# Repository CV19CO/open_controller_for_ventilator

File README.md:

# Open source controller board for ventilators

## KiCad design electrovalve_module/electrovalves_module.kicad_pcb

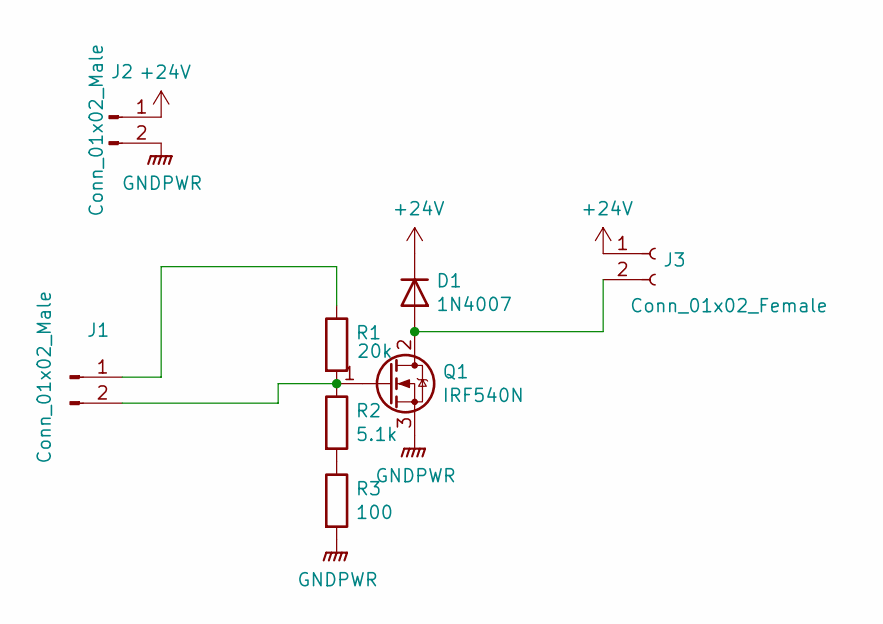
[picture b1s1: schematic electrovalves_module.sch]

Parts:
D1: 1N4007; D_DO-41_SOD81_P10.16mm_Horizontal
J1, J2: Conn_01x02_Male; TerminalBlock_bornier-2_P5.08mm
J3: Conn_01x02_Female; TerminalBlock_bornier-2_P5.08mm
Q1: IRF540N; TO-220-3_Vertical
R1: 20k; R_Axial_DIN0207_L6.3mm_D2.5mm_P7.62mm_Horizontal
R2: 5.1k; R_Axial_DIN0207_L6.3mm_D2.5mm_P7.62mm_Horizontal
R3: 100; R_Axial_DIN0207_L6.3mm_D2.5mm_P7.62mm_Horizontal

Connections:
+24V: D1.1 (K), J2.1, J3.1
GNDPWR: J2.2, Q1.3 (S), R3.2
unnamed: D1.2 (A), J3.2, Q1.2 (D)
unnamed: J1.1, R1.1
unnamed: J1.2, Q1.1 (G), R1.2, R2.1
unnamed: R2.2, R3.1

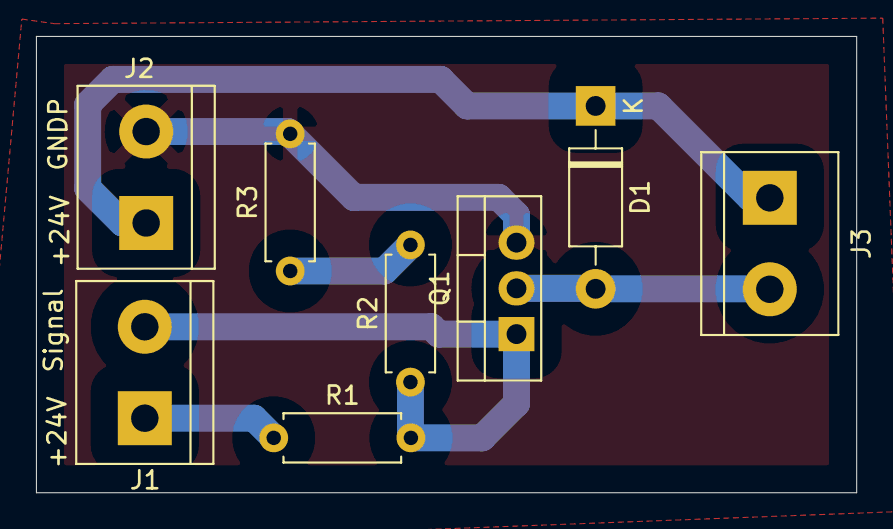
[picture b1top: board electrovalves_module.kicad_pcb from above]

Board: 2 copper layers, 45.6 x 25.3 mm, 8 parts (0 on the bottom side), 6 nets.

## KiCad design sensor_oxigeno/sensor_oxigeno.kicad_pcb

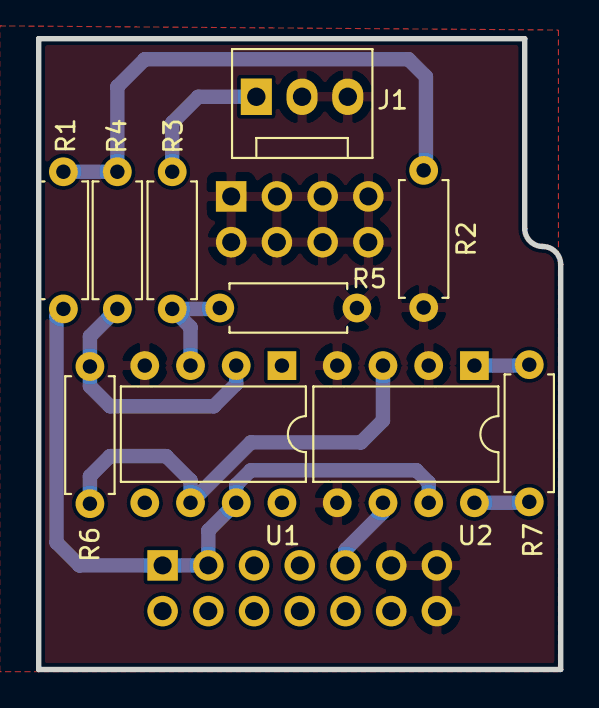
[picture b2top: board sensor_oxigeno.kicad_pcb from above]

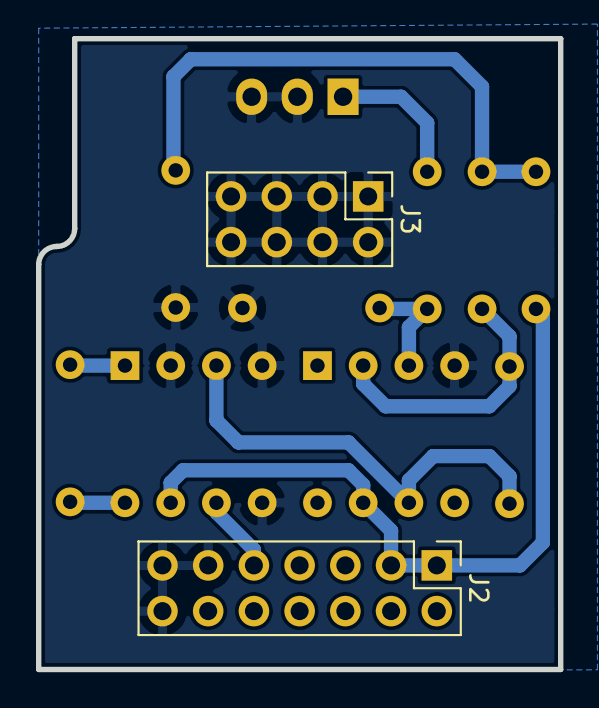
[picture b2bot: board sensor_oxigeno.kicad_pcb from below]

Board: 4 copper layers, 29.0 x 35.0 mm, 12 parts (2 on the bottom side), 10 nets.

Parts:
J1: Conn_01x02_Female; FanPinHeader_1x03_P2.54mm_Vertical
J2: Conn_02x07_Odd_Even; PinHeader_2x07_P2.54mm_Vertical
J3: Conn_02x04_Odd_Even; PinHeader_2x04_P2.54mm_Vertical
R1: 25.3 k; R_Axial_DIN0207_L6.3mm_D2.5mm_P7.62mm_Horizontal
R2: 100; R_Axial_DIN0207_L6.3mm_D2.5mm_P7.62mm_Horizontal
R3, R4, R5, R6: 10k; R_Axial_DIN0207_L6.3mm_D2.5mm_P7.62mm_Horizontal
R7: 50; R_Axial_DIN0207_L6.3mm_D2.5mm_P7.62mm_Horizontal
U1: LM318N; DIP-8_W7.62mm
U2: INA128; DIP-8_W7.62mm

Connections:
+3V3: J2.1, J2.3, R1.2, U1.7, U2.7
/Analog: J2.9, U2.6
GND: J1.2, J1.3, J2.11, J2.13, J2.14, J3.1, J3.2, J3.3, J3.4, J3.5, J3.6, J3.7, J3.8, R2.2, R5.1, U1.4, U2.2, U2.4, U2.5
unnamed: J1.1, R3.2
unnamed: R1.1, R2.1, R4.2
unnamed: R3.1, R5.2, U1.3
unnamed: R4.1, R6.2, U1.2
unnamed: R6.1, U1.6, U2.3
unnamed: R7.1, U2.1
unnamed: R7.2, U2.8

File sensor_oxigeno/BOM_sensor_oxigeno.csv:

"Source:","/home/jaiber/proyectos/respirador/repos/open_controller_for_ventilator/sensor_oxigeno/sensor_oxigeno.sch"
"Date:","jue 26 may 2022 21:42:56"
"Tool:","Eeschema 5.1.12-84ad8e8a86~92~ubuntu20.04.1"
"Generator:","/usr/share/kicad/plugins/bom_csv_grouped_by_value.py"
"Component Count:","12"

"Individual Components:"

"Item","Qty","Reference(s)","Value","LibPart","Footprint","Datasheet"
"","","J1","Conn_01x02_Female","Connector:Conn_01x03_Male","Connector:FanPinHeader_1x03_P2.54mm_Vertical","~"
"","","J2","Conn_02x07_Odd_Even","Connector_Generic:Conn_02x07_Odd_Even","Connector_PinHeader_2.54mm:PinHeader_2x07_P2.54mm_Vertical","~"
"","","J3","Conn_02x04_Odd_Even","Connector_Generic:Conn_02x04_Odd_Even","Connector_PinHeader_2.54mm:PinHeader_2x04_P2.54mm_Vertical","~"
"","","R1","25.3 k","Device:R","Resistor_THT:R_Axial_DIN0207_L6.3mm_D2.5mm_P7.62mm_Horizontal","~"
"","","R2","100","Device:R","Resistor_THT:R_Axial_DIN0207_L6.3mm_D2.5mm_P7.62mm_Horizontal","~"
"","","R3","10k","Device:R","Resistor_THT:R_Axial_DIN0207_L6.3mm_D2.5mm_P7.62mm_Horizontal","~"
"","","R4","10k","Device:R","Resistor_THT:R_Axial_DIN0207_L6.3mm_D2.5mm_P7.62mm_Horizontal","~"
"","","R5","10k","Device:R","Resistor_THT:R_Axial_DIN0207_L6.3mm_D2.5mm_P7.62mm_Horizontal","~"
"","","R6","10k","Device:R","Resistor_THT:R_Axial_DIN0207_L6.3mm_D2.5mm_P7.62mm_Horizontal","~"
"","","R7","50","Device:R","Resistor_THT:R_Axial_DIN0207_L6.3mm_D2.5mm_P7.62mm_Horizontal","~"
"","","U1","LM318N","Amplifier_Operational:LM318N","Package_DIP:DIP-8_W7.62mm","http://www.ti.com/lit/ds/symlink/lm318-n.pdf"
"","","U2","INA128","Amplifier_Instrumentation:INA128","Package_DIP:DIP-8_W7.62mm","http://www.ti.com/lit/ds/symlink/ina128.pdf"



"Collated Components:"

"Item","Qty","Reference(s)","Value","LibPart","Footprint","Datasheet"
"1","1","J1","Conn_01x02_Female","Connector:Conn_01x03_Male","Connector:FanPinHeader_1x03_P2.54mm_Vertical","~"
"2","1","J2","Conn_02x07_Odd_Even","Connector_Generic:Conn_02x07_Odd_Even","Connector_PinHeader_2.54mm:PinHeader_2x07_P2.54mm_Vertical","~"
"3","1","J3","Conn_02x04_Odd_Even","Connector_Generic:Conn_02x04_Odd_Even","Connector_PinHeader_2.54mm:PinHeader_2x04_P2.54mm_Vertical","~"
"4","1","R1","25.3 k","Device:R","Resistor_THT:R_Axial_DIN0207_L6.3mm_D2.5mm_P7.62mm_Horizontal","~"
"5","1","R2","100","Device:R","Resistor_THT:R_Axial_DIN0207_L6.3mm_D2.5mm_P7.62mm_Horizontal","~"
"6","4","R3, R4, R5, R6","10k","Device:R","Resistor_THT:R_Axial_DIN0207_L6.3mm_D2.5mm_P7.62mm_Horizontal","~"
"7","1","R7","50","Device:R","Resistor_THT:R_Axial_DIN0207_L6.3mm_D2.5mm_P7.62mm_Horizontal","~"
"8","1","U1","LM318N","Amplifier_Operational:LM318N","Package_DIP:DIP-8_W7.62mm","http://www.ti.com/lit/ds/symlink/lm318-n.pdf"
"9","1","U2","INA128","Amplifier_Instrumentation:INA128","Package_DIP:DIP-8_W7.62mm","http://www.ti.com/lit/ds/symlink/ina128.pdf"

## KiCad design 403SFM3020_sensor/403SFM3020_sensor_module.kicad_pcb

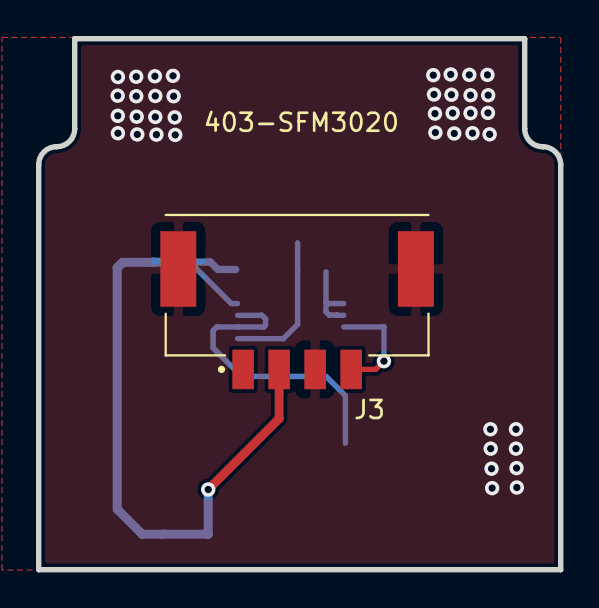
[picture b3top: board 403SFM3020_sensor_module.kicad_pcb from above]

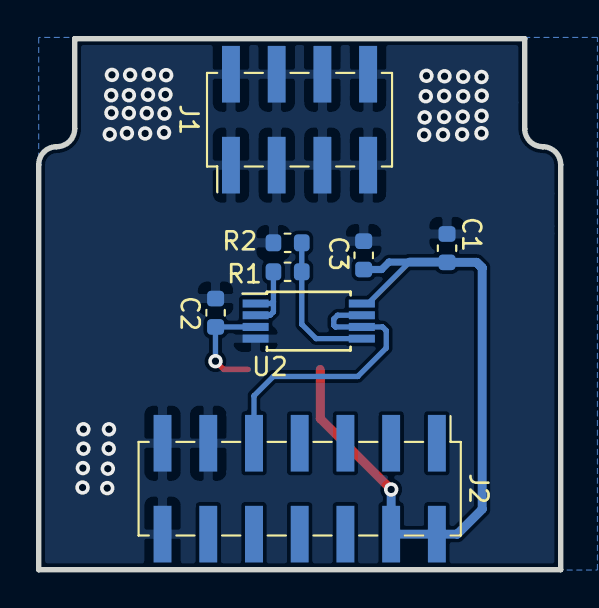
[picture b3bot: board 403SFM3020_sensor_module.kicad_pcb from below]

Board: 4 copper layers, 29.0 x 29.5 mm, 9 parts (8 on the bottom side), 7 nets.

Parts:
C1, C3: 0.1u; C_0603_1608Metric
C2: 1n; C_0603_1608Metric
J1: Conn_02x04_Odd_Even; PinHeader_2x04_P2.54mm_Vertical_SMD
J2: Conn_02x07_Odd_Even; PinHeader_2x07_P2.54mm_Vertical_SMD
J3: Conn_01x05_Female; MOLEX_5600200430
R1: 11k3; R_0603_1608Metric
R2: 22k; R_0603_1608Metric
U2: LM358; TSSOP-8_4.4x3mm_P0.65mm

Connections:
+3V3: J2.1, J2.3
+5V: C1.1, C3.1, J2.2, J2.4, J3.2, U2.8
/Analog: J2.9, U2.6, U2.7
GND: C1.2, C2.2, C3.2, J1.1, J1.2, J1.3, J1.4, J1.5, J1.6, J1.7, J1.8, J2.11, J2.13, J2.14, J3.3, J3.S1, J3.S2, R2.2, U2.4
unnamed: C2.1, J3.4, U2.3
unnamed: R1.1, R2.1, U2.5
unnamed: R1.2, U2.1, U2.2

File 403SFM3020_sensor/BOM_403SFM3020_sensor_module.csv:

Item,Qty,Reference(s),Value,Footprint,DigiKey
1,2,"C1, C3",0.1u,Capacitor_SMD:C_0603_1608Metric,732-7939-1-ND
2,1,C2,1n,Capacitor_SMD:C_0603_1608Metric,311-4053-1-ND
3,1,J1,Conn_02x04_Odd_Even,Connector_PinHeader_2.54mm:PinHeader_2x04_P2.54mm_Vertical_SMD,609-6367-ND
4,1,J2,Conn_02x07_Odd_Even,Connector_PinHeader_2.54mm:PinHeader_2x07_P2.54mm_Vertical_SMD,609-6365-ND
5,1,J3,Conn_01x05_Female,SMD_project:MOLEX_5600200430,WM17822CT-ND
6,1,J3,Conn_01x05_Female,SMD_project:MOLEX_5600200430,WM8688-ND
7,8,J3,Conn_01x05_Female,SMD_project:MOLEX_5600200430,WM4561CT-ND
8,1,R1,11k3,Resistor_SMD:R_0603_1608Metric,A102208CT-ND
9,1,R2,22k,Resistor_SMD:R_0603_1608Metric,A103066CT-ND
10,1,U2,LM358,Package_SO:TSSOP-8_4.4x3mm_P0.65mm,296-51268-1-ND

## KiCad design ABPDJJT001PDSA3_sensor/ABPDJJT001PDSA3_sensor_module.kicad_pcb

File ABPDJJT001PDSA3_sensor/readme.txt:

Sensor: ABPDJJT001PDSA3 
Mouser: https://co.mouser.com/ProductDetail/785-ABPDJJT001PDSA3
Datasheet: https://co.mouser.com/datasheet/2/187/honeywell-sensing-basic-board-mount-pressure-abp-s-1662208.pdf

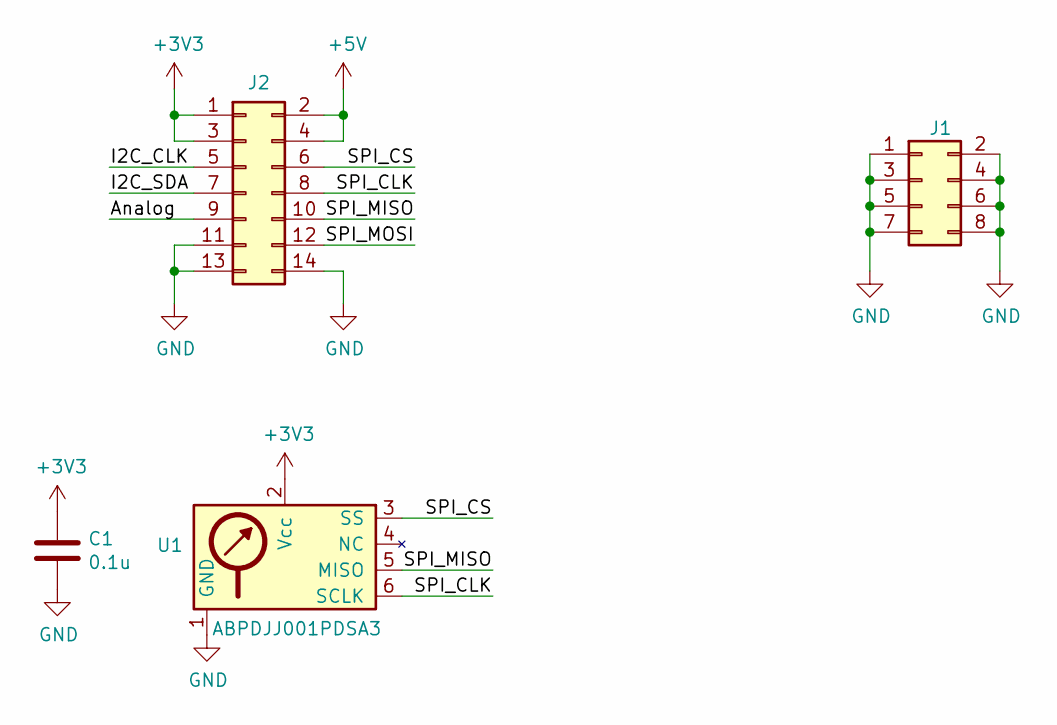
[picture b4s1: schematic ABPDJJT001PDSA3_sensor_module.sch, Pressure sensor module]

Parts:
C1: 0.1u; C_0603_1608Metric; DigiKey 1276-1258-1-ND
J1: Conn_02x04_Odd_Even; PinHeader_2x04_P2.54mm_Vertical_SMD; DigiKey 609-6367-ND
J2: Conn_02x07_Odd_Even; PinHeader_2x07_P2.54mm_Vertical_SMD; DigiKey 609-6365-ND
U1: ABPDJJ001PDSA3; DIP_JJ

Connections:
+3V3: C1.1, J2.1, J2.3, U1.2 (Vcc)
+5V: J2.2, J2.4
/Analog: J2.9
/I2C_CLK: J2.5
/I2C_SDA: J2.7
/SPI_CLK: J2.8, U1.6 (SCLK)
/SPI_CS: J2.6, U1.3 (SS)
/SPI_MISO: J2.10, U1.5 (MISO)
/SPI_MOSI: J2.12
GND: C1.2, J1.1, J1.2, J1.3, J1.4, J1.5, J1.6, J1.7, J1.8, J2.11, J2.13, J2.14, U1.1 (GND)

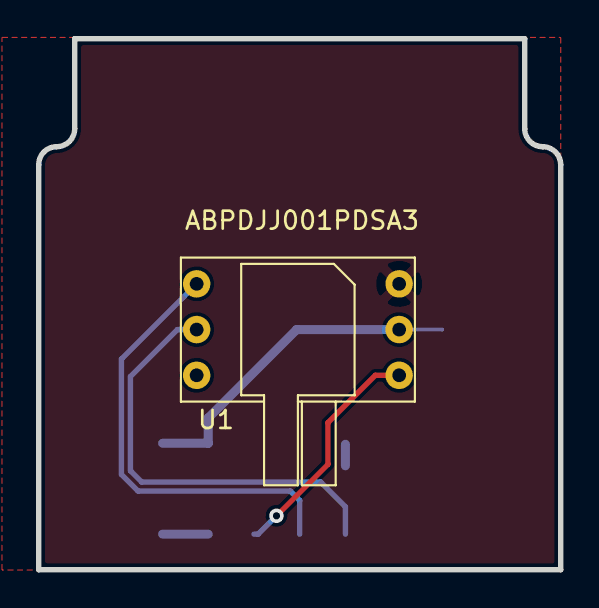
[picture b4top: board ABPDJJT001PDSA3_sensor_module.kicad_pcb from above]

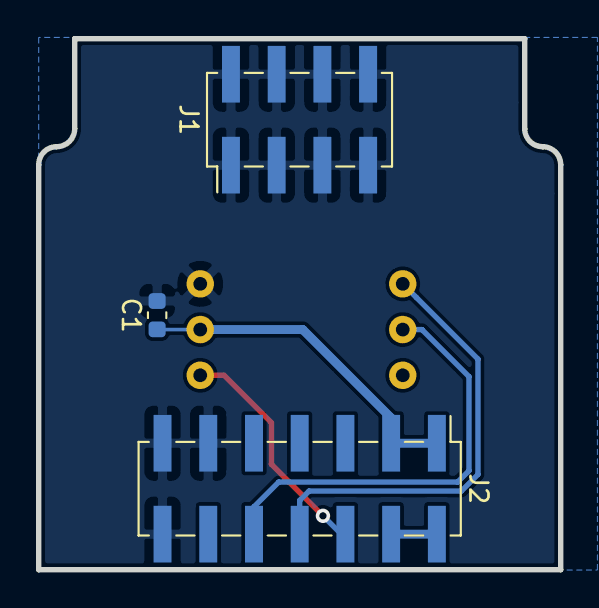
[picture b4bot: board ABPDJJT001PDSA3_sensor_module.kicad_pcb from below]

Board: 4 copper layers, 29.0 x 29.5 mm, 4 parts (3 on the bottom side), 6 nets.

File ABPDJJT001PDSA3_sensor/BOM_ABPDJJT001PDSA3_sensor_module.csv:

Reference, Quantity, Value, Footprint, Datasheet, DigiKey
C1 ,1,"0.1u","Capacitor_SMD:C_0603_1608Metric","~","1276-1258-1-ND"
J1 ,1,"Conn_02x04_Odd_Even","Connector_PinHeader_2.54mm:PinHeader_2x04_P2.54mm_Vertical_SMD","~","609-6367-ND"
J2 ,1,"Conn_02x07_Odd_Even","Connector_PinHeader_2.54mm:PinHeader_2x07_P2.54mm_Vertical_SMD","~","609-6365-ND"
U1 ,1,"ABPDJJ001PDSA3","TH_project:DIP_JJ",""

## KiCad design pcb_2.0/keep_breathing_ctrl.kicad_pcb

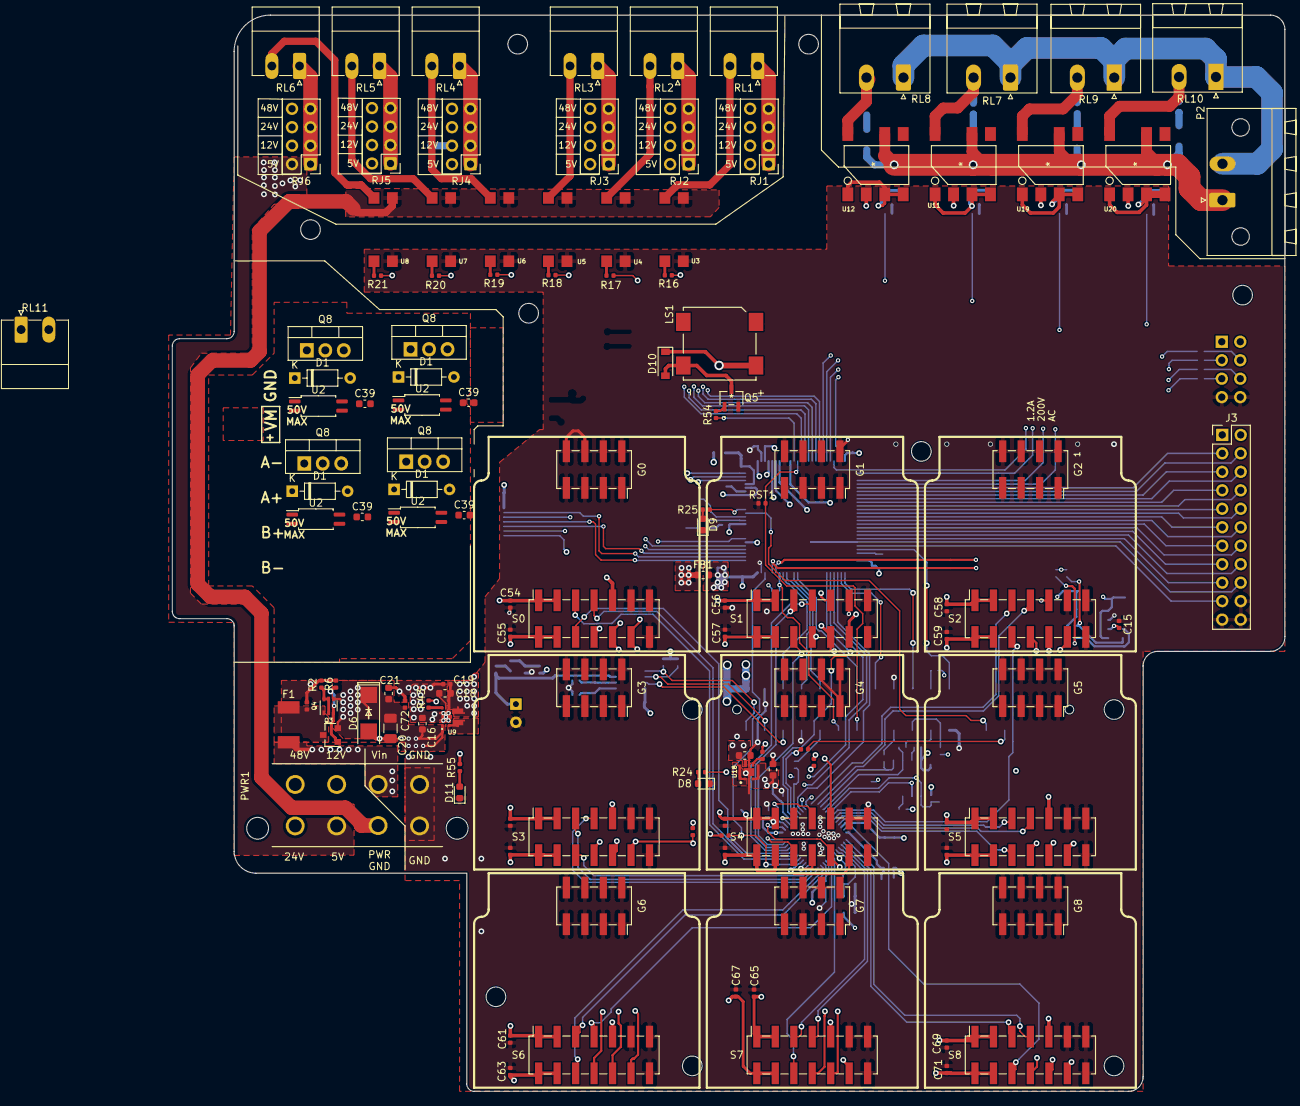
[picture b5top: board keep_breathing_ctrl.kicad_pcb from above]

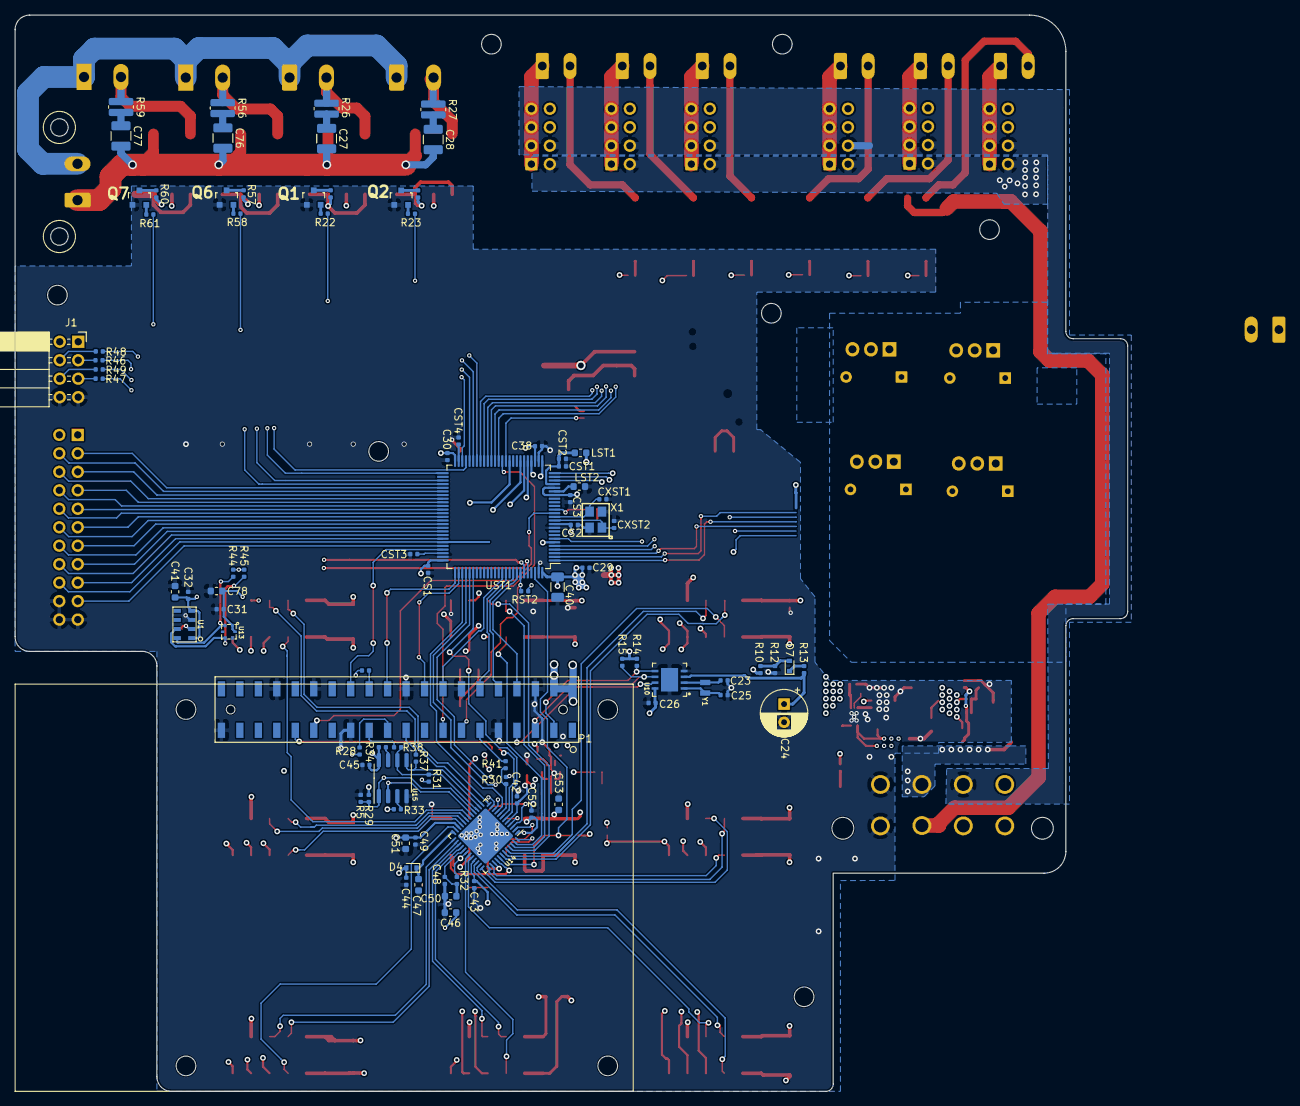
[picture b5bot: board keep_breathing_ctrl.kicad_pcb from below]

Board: 4 copper layers, 153.0 x 148.0 mm, 226 parts (91 on the bottom side), 190 nets.

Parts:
C15, C31, C32: 100nF; C_0402_1005Metric
C16, C18: 10u; C_0603_1608Metric
C17: 1uF; C_0402_1005Metric
C19, C42, C44: 0.1u; C_0402_1005Metric
C20: 100uF; R_1206_3216Metric
C21: 47uF; R_0603_1608Metric
C23, C25: 4pF; C_0402_1005Metric
C24: JUWT1105MCD; CP_Radial_D6.3mm_P2.50mm
C26, C29, C30, C38, C54, C55, C56, C57, C58, C59, C60, C61, C62, C63, C64, C65, C66, C67, C68, C69, C70, C71: 0.1uF; C_0402_1005Metric
C27, C28, C76, C77: 0.1u 250V; C_1210_3225Metric
C39, C39#2, C39#3, C39#4: 1uF; C_0603_1608Metric
C40: 4.7uF; C_1206_3216Metric
C41, C75, C78: 10uF; C_0603_1608Metric
C43, C45, C48, C49, C52: 0.1u; R_0402_1005Metric
C46, C50, C51, C53: 4.7u; R_0603_1608Metric
C47, C73: 4.7u; C_0603_1608Metric
C72: 100nF; R_0402_1005Metric
CS1, CS2, CS3: 0.1uF; C_0402_1005Metric
CST1: 0.1uF; C_0402_1005Metric
CST2: 1uF; C_0402_1005Metric
CST3, CST4: 2.2uF; C_0402_1005Metric
CXST1, CXST2: 22pF; C_0402_1005Metric
D1, D1#2, D1#3, D1#4: 1N4148; D_DO-35_SOD27_P7.62mm_Horizontal
D4: CDBU0520; D_SOD-523
D6: SMBJ5.0A-TR; DO-214AA
D7: 1SS389,L3F; D_SOD-523
D8, D9, D11: LED; LED_0603_1608Metric
D10: 1N4148; D_SOD-123
F1: MF-MSMF250/X; PTC
FB1: Ferrite_Bead_Small; R_0603_1608Metric
G0, G1, G2, G3, G4, G5, G6, G7, G8: Conn_01x03; PinSocket_2x04_P2.54mm_Vertical_SMD
H1, H2, H3, H4, H5, H6, H7, H8, H9, H10, H11: MountingHole; MountingHole_2.7mm_M2.5
J1: Conn_02x04_Odd_Even; PinSocket_2x04_P2.54mm_Horizontal
J3: Conn_02x11_Odd_Even; PinHeader_2x11_P2.54mm_Vertical
LS1: CSS-95B30-SMT; CUI_CSS-95B30-SMT
LST1, LST2: 2A 120 ohm; R_0603_1608Metric
P1: CONN_RASPBERRY; SMD_CONN_2x20
P2: Conn_01x04_Female; PhoenixContact_MSTB_2,5_2-GF_1x02_P5.00mm_Horizontal_Thread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
PWR1: Conn_01x03; 10142708-08200LF
Q1, Q2, Q6, Q7: PN2222; SOT23_Transistor
Q3: DMG2305UX; SOT-23
Q4: BCM857BS; SOT-363_SC-70-6
Q5: 2SC3325-Y
Q8, Q8#2, Q8#3, Q8#4: IRF540N; TO-220-3_Vertical
R2, R42, R43, R44, R45: 10k; R_0402_1005Metric
R5, R29, R30, R31, R33, R34, R50, R51, R53: 10K; R_0402_1005Metric
R6: 47k; R_0402_1005Metric
R10: 450; R_0402_1005Metric
R12: 500; R_0402_1005Metric
R13, R28, R32, R37, R38, R40, R41, R46, R47, R48, R49, R52: 100; R_0402_1005Metric
R14, R15: 2.2k; R_0402_1005Metric
R16, R17, R18, R19, R20, R21, R23, R61: 200; R_0402_1005Metric
R22, R58: 330; R_0402_1005Metric
R24, R25, R55: 1k; R_0402_1005Metric
R26, R27, R56, R59: 100 1/2W; R_0612_1632Metric
R35, R36, R57, R60: 22; R_0402_1005Metric
R54: 180; R_0402_1005Metric
RJ1, RJ2, RJ3, RJ4, RJ5, RJ6: Conn_02x04_Odd_Even; PinHeader_2x04_P2.54mm_Vertical
RL1, RL2, RL3, RL4, RL5, RL6, RL11: Conn_01x04_Female; PhoenixContact_MC_1,5_2-G-3.81_1x02_P3.81mm_Horizontal
RL7, RL8, RL9, RL10: Conn_01x04_Female; PhoenixContact_MSTBA_2,5_2-G-5,08_1x02_P5.08mm_Horizontal
RST1, RST2: 10k; R_0402_1005Metric
S0, S1, S2, S3, S4, S5, S6, S7, S8: Conn_02x07_Counter_Clockwise; PinSocket_2x07_P2.54mm_Vertical_SMD
U1: MPL3115A2; 8LGA
U2, U2#2, U2#3, U2#4: TLP291; SOIC-4_4.55x2.6mm_P1.27mm
U3, U4, U5, U6, U7, U8: TLP240D; TLP240D_TP1
U9: XCL214B333; TOREX_XCL214B123DR
U10: PCF8523TK; HVSON8
U11, U12, U19, U20: AQH3223AX; AQH3223A
U13: HTS221; HLGA-6L
U14: ICE40UP5K-SG48ITR; QFN-48-1EP_7x7mm_P0.5mm_EP5.6x5.6mm
U15: GD25Q32CTIGR-Memory_Flash; SOIC-8_3.9x4.9mm_P1.27mm
U18: XCL206B123; CL-2025-02
UST1: STM32F427VIT6; LQFP-100_14x14mm_P0.5mm
X1: ABM8G
Y1: ABS06-107-32.768KHZ-T; ABS06-107

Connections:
1V2_ICE: C42.1, C75.1, R32.2, U14.5, U14.30, U18.3, U18.8
3V3_STM: C29.1, C30.1, C38.1, C39#4.1, C40.1, CS1.1, CS2.1, CS3.1, FB1.2, LST1.1, RST2.1, UST1.6, UST1.11, UST1.19, UST1.21, UST1.28, UST1.50, UST1.75, UST1.100
5V_R: PWR1.5, RJ1.2, RJ2.2, RJ3.2, RJ4.2, RJ5.2, RJ6.2
12V_R: PWR1.6, RJ1.4, RJ2.4, RJ3.4, RJ4.4, RJ5.4, RJ6.4
24V_R: PWR1.7, RJ1.6, RJ2.6, RJ3.6, RJ4.6, RJ5.6, RJ6.6
48V_R: PWR1.8, RJ1.8, RJ2.8, RJ3.8, RJ4.8, RJ5.8, RJ6.8
+2V5: C47.1, D4.1, U14.24
+3V3: C18.1, C19.1, C26.2, C31.1, C32.1, C41.1, C43.1, C44.1, C45.1, C46.1, C49.1, C51.1, C52.1, C53.1, C54.1, C56.1, C58.1, C60.1, C61.1, C64.1, C65.1, C68.1, C69.1, C78.1, D4.2, FB1.1, J1.1, J3.1, R14.2, R15.2, R29.2, R30.2, R31.2, R33.2, R34.2, R44.1, R45.1, R50.2, R51.2, R53.2, S0.1, S0.3, S1.1, S1.3, S2.1, S2.3, S3.1, S3.3, S4.1, S4.3, S5.1, S5.3, S6.1, S6.3, S7.1, S7.3, S8.1, S8.3, U1.1, U1.4, U9.4, U9.9, U10.8, U11.2, U12.2, U13.1, U13.6, U14.1, U14.22, U14.33, U15.8, U19.2, U20.2
+5V: C16.1, C20.1, C21.1, C55.1, C57.1, C59.1, C62.1, C63.1, C66.1, C67.1, C70.1, C71.1, C72.1, C73.1, D6.1, D10.1, J1.2, J3.2, LS1.P, P1.2, P1.4, Q3.2, Q4.4, R10.2, R42.2, R43.2, R55.2, S0.2, S0.4, S1.2, S1.4, S2.2, S2.4, S3.2, S3.4, S4.2, S4.4, S5.2, S5.4, S6.2, S6.4, S7.2, S7.4, S8.2, S8.4, U9.1, U18.6
/I2C/I2C_SCL: P1.5, R15.1, U10.6
/I2C/I2C_SDA: P1.3, R14.1, U10.5
/PSU/L1_Lx_1V2: U18.1, U18.7
/PSU/L1_Lx_3V3: U9.3, U9.8
/PSU/Q3S: C17.1, F1.2, Q3.3, Q4.1
/PSU/Vin: F1.1, PWR1.4
/Rapsberry/BOOT0: P1.13, RST2.2, UST1.94
/Rapsberry/BOOT1: P1.15, RST1.2, UST1.37
/Rapsberry/ICE_DONE: P1.31, R52.1
/Rapsberry/INT_RTC: P1.7, U10.7
/Rapsberry/JNRST: P1.12, UST1.90
/Rapsberry/JTCK: P1.22, UST1.76
/Rapsberry/JTDI: P1.18, UST1.77
/Rapsberry/JTDO: P1.16, UST1.89
/Rapsberry/JTMS: P1.26, UST1.72
/Rapsberry/MCU_NRST: P1.29, UST1.14
/Rapsberry/RST_ICE: P1.11, R41.1
/Rapsberry/RX_PI: P1.10, UST1.92
/Rapsberry/SPI_CLK: P1.23, R38.1
/Rapsberry/SPI_CS: P1.24, R40.1
/Rapsberry/SPI_MISO: P1.21, R28.1
/Rapsberry/SPI_MOSI: P1.19, R37.1
/STM32F4/Buzzer: R54.2, UST1.36
/STM32F4/LED: R25.2, UST1.15
/STM32F4/PA8: J3.15, UST1.67
/STM32F4/PA9: J3.16, UST1.68
/STM32F4/PA10: J3.17, UST1.69
/STM32F4/PA11: J3.18, UST1.70
/STM32F4/PA12: J3.19, UST1.71
/STM32F4/PC6: J3.11, UST1.63
/STM32F4/PC7: J3.12, UST1.64
/STM32F4/PC8: J3.13, UST1.65
/STM32F4/PC9: J3.14, UST1.66
/STM32F4/PD8: J3.3, UST1.55
/STM32F4/PD9: J3.4, UST1.56
/STM32F4/PD10: J3.5, UST1.57
/STM32F4/PD11: J3.6, UST1.58
/STM32F4/PD12: J3.7, UST1.59
/STM32F4/PD13: J3.8, UST1.60
/STM32F4/PD14: J3.9, UST1.61
/STM32F4/PD15: J3.10, UST1.62
/STM32F4/P_EV7: R21.2, UST1.38
/STM32F4/P_EV8: R20.2, UST1.39
/STM32F4/P_EV9: R19.2, UST1.40
/STM32F4/P_EV10: R18.2, UST1.41
/STM32F4/P_EV11: R17.2, UST1.42
/STM32F4/P_EV12: R16.2, UST1.43
/STM32F4/P_EV13: R23.2, UST1.44
/STM32F4/P_EV14: R22.2, UST1.45
/STM32F4/P_EV15: R58.2, UST1.46
/STM32F4/P_EV16: R61.2, UST1.48
/STM32F4/SPI2_MISO: R49.1, UST1.53
/STM32F4/SPI2_MOSI: R47.2, UST1.54
/STM32F4/SPI2_NSS_0: R46.2, UST1.51
/STM32F4/SPI2_SCK: R48.1, UST1.47
/STM32F4/SPI3_MISO: U14.10, UST1.79
/STM32F4/SPI3_MOSI: U14.11, UST1.80
/STM32F4/SPI3_NSS: U14.6, UST1.81
/STM32F4/SPI3_SCK: U14.9, UST1.78
/STM32F4/SPI4_NSS_1: R53.1, U14.41, UST1.98
/STM32F4/STM_UART_RX: P1.8, UST1.93
/STM32F4/VDDAST: CST1.1, CST2.1, LST1.2, UST1.22
/SensorShields/ANALOG_0: S0.9, UST1.25
/SensorShields/ANALOG_1: S1.9, UST1.26
/SensorShields/ANALOG_2: S2.9, UST1.35
/SensorShields/ANALOG_3: S3.9, UST1.24
/SensorShields/ANALOG_4: S4.9, UST1.29
/SensorShields/ANALOG_5: S5.9, UST1.32
/SensorShields/ANALOG_6: S6.9, UST1.23
/SensorShields/ANALOG_7: S7.9, UST1.30
/SensorShields/ANALOG_8: S8.9, UST1.31
/SensorShields/CDONE: R24.2, R52.2, U14.7
/SensorShields/CRESET_N: R30.1, R41.2, U14.8
/SensorShields/FPGA_SI: R28.2, U14.17, U15.2
/SensorShields/FPGA_SO: R37.2, U14.14, U15.5
/SensorShields/FT_SCK: R31.1, R38.2, U14.15, U15.6
/SensorShields/FT_SSn: R5.2, R29.1, R40.2, U14.16, U15.1
/SensorShields/I2C_CLK_0: S0.5, U14.42
/SensorShields/I2C_CLK_1: S1.5, U14.46
/SensorShields/I2C_CLK_2: S2.5, U14.12
/SensorShields/I2C_CLK_3: S3.5, U14.37
/SensorShields/I2C_CLK_4: S4.5, U14.4
/SensorShields/I2C_CLK_5: S5.5, U14.19
/SensorShields/I2C_CLK_6: S6.5, U14.34
/SensorShields/I2C_CLK_7: S7.5, U14.28
/SensorShields/I2C_CLK_8: S8.5, U14.26
/SensorShields/I2C_SDA_0: S0.7, U14.43
/SensorShields/I2C_SDA_1: S1.7, U14.45
/SensorShields/I2C_SDA_2: S2.7, U14.13
/SensorShields/I2C_SDA_3: S3.7, U14.36
/SensorShields/I2C_SDA_4: S4.7, U14.3
/SensorShields/I2C_SDA_5: S5.7, U14.20
/SensorShields/I2C_SDA_6: S6.7, U14.32
/SensorShields/I2C_SDA_7: S7.7, U14.27
/SensorShields/I2C_SDA_8: S8.7, U14.25
/SensorShields/SPI_CLK: R50.1, S0.8, S1.8, S2.8, S3.8, S4.8, S5.8, S6.8, S7.8, S8.8, U14.39
/SensorShields/SPI_CS_0: S0.6, U14.44
/SensorShields/SPI_CS_1: S1.6, U14.47
/SensorShields/SPI_CS_2: S2.6, U14.18
/SensorShields/SPI_CS_3: S3.6, U14.38
/SensorShields/SPI_CS_4: S4.6, U14.48
/SensorShields/SPI_CS_5: S5.6, U14.21
/SensorShields/SPI_CS_6: S6.6, U14.35
/SensorShields/SPI_CS_7: S7.6, U14.31
/SensorShields/SPI_CS_8: S8.6, U14.23
/SensorShields/SPI_MISO: S0.10, S1.10, S2.10, S3.10, S4.10, S5.10, S6.10, S7.10, S8.10, U14.2
/SensorShields/SPI_MOSI: R51.1, S0.12, S1.12, S2.12, S3.12, S4.12, S5.12, S6.12, S7.12, S8.12, U14.40
/SensorShields/VCC_PLL: C48.1, C50.1, R32.1, U14.29
/Sensors/SCL: R44.2, U1.8, U13.2, UST1.95
/Sensors/SDA: R45.2, U1.7, U13.4, UST1.96
GND: C15.2, C16.2, C17.2, C18.2, C19.2, C20.2, C21.2, C23.1, C24.2, C25.2, C26.1, C29.2, C30.2, C31.2, C32.2, C38.2, C39#4.2, C40.2, C41.2, C42.2, C43.2, C44.2, C45.2, C46.2, C47.2, C48.2, C49.2, C50.2, C51.2, C52.2, C53.2, C54.2, C55.2, C56.2, C57.2, C58.2, C59.2, C60.2, C61.2, C62.2, C63.2, C64.2, C65.2, C66.2, C67.2, C68.2, C69.2, C70.2, C71.2, C72.2, C73.2, C75.2, C78.2, CS1.2, CS2.2, CS3.2, CST1.2, CST2.2, CST3.1, CST4.1, CXST1.2, CXST2.2, D6.2, D8.1, D9.1, D11.1, G0.1, G0.2, G0.3, G0.4, G0.5, G0.6, G0.7, G0.8, G1.1, G1.2, G1.3, G1.4, G1.5, G1.6, G1.7, G1.8, G2.1, G2.2, G2.3, G2.4, G2.5, G2.6, G2.7, G2.8, G3.1, G3.2, G3.3, G3.4, G3.5, G3.6, G3.7, G3.8, G4.1, G4.2, G4.3, G4.4, G4.5, G4.6, G4.7, G4.8, G5.1, G5.2, G5.3, G5.4, G5.5, G5.6, G5.7, G5.8, G6.1, G6.2, G6.3, G6.4, G6.5, G6.6, G6.7, G6.8, G7.1, G7.2, G7.3, G7.4, G7.5, G7.6, G7.7, G7.8, G8.1, G8.2, G8.3, G8.4, G8.5, G8.6, G8.7, G8.8, J1.7, J1.8, J3.20, J3.21, J3.22, LST2.2, P1.6, P1.9, P1.14, P1.20, P1.25, P1.30, P1.34, P1.39, PWR1.1, PWR1.2, Q1.1, Q2.1, Q5.2, Q6.1, Q7.1, R2.2, R5.1, R6.2, R12.1, RST1.1, S0.11, S0.13, S0.14, S1.11, S1.13, S1.14, S2.11, S2.13, S2.14, S3.11, S3.13, S3.14, S4.11, S4.13, S4.14, S5.11, S5.13, S5.14, S6.11, S6.13, S6.14, S7.11, S7.13, S7.14, S8.11, S8.13, S8.14, U1.3, U2#4.2, U3.2, U4.2, U5.2, U6.2, U7.2, U8.2, U9.5, U9.7, U10.4, U10.PAD, U13.5, U14.49, U15.4, U18.2, U18.5, U18.PAD, UST1.10, UST1.27, UST1.74, UST1.99, X1.2, X1.4
GNDPWR: PWR1.3, Q8#4.3, U3.3, U4.3, U5.3, U6.3, U7.3, U8.3
LINE: P2.2, RL7.1, RL8.1, RL9.1, RL10.1
NEUT: C27.2, C28.2, C76.2, C77.2, P2.1, U11.6, U12.6, U19.6, U20.6
unnamed: C15.1, U1.2
unnamed: C23.2, U10.2, Y1.1
unnamed: C24.1, R13.1, U10.3
unnamed: C25.1, U10.1, Y1.2
unnamed: C27.1, R26.2
unnamed: C28.1, R27.2
unnamed: C76.1, R56.2
unnamed: C77.1, R59.2
unnamed: CST3.2, UST1.73
unnamed: CST4.2, UST1.49
unnamed: CXST1.1, UST1.13, X1.3
unnamed: CXST2.1, UST1.12, X1.1
unnamed: D1#4.1, RL11.1
unnamed: D1#4.2, Q8#4.2, RL11.2
unnamed: D7.1, R13.2
unnamed: D7.2, R10.1, R12.2
unnamed: D8.2, R24.1
unnamed: D9.2, R25.1
unnamed: D10.2, LS1.N, Q5.3
unnamed: D11.2, R55.1
unnamed: J1.3, R46.1
unnamed: J1.4, R48.2
unnamed: J1.5, R47.1
unnamed: J1.6, R49.2
unnamed: LST2.1, UST1.20
unnamed: Q1.2, R22.1
unnamed: Q1.3, R35.2
unnamed: Q2.2, R23.1
unnamed: Q2.3, R36.2
unnamed: Q3.1, Q4.3, R6.1
unnamed: Q4.2, Q4.5, Q4.6, R2.1
unnamed: Q5.1, R54.1
unnamed: Q6.2, R58.1
unnamed: Q6.3, R57.2
unnamed: Q7.2, R61.1
unnamed: Q7.3, R60.2
unnamed: Q8#4.1, U2#4.3
unnamed: R16.1, U3.1
unnamed: R17.1, U4.1
unnamed: R18.1, U5.1
unnamed: R19.1, U6.1
unnamed: R20.1, U7.1
unnamed: R21.1, U8.1
unnamed: R26.1, RL7.2, U11.8
unnamed: R27.1, RL8.2, U12.8
unnamed: R33.1, U15.3
unnamed: R34.1, U15.7
unnamed: R35.1, U11.1, U11.3, U11.4
unnamed: R36.1, U12.1, U12.3, U12.4
unnamed: R42.1, U18.4
unnamed: R43.1, U9.6
unnamed: R56.1, RL9.2, U19.8
unnamed: R57.1, U19.1, U19.3, U19.4
unnamed: R59.1, RL10.2, U20.8
unnamed: R60.1, U20.1, U20.3, U20.4
unnamed: RJ1.1, RJ1.3, RJ1.5, RJ1.7, RL1.1
unnamed: RJ2.1, RJ2.3, RJ2.5, RJ2.7, RL2.1
unnamed: RJ3.1, RJ3.3, RJ3.5, RJ3.7, RL3.1
unnamed: RJ4.1, RJ4.3, RJ4.5, RJ4.7, RL4.1
unnamed: RJ5.1, RJ5.3, RJ5.5, RJ5.7, RL5.1
unnamed: RJ6.1, RJ6.3, RJ6.5, RJ6.7, RL6.1
unnamed: RL1.2, U3.4
unnamed: RL2.2, U4.4
unnamed: RL3.2, U5.4
unnamed: RL4.2, U6.4
unnamed: RL5.2, U7.4
unnamed: RL6.2, U8.4

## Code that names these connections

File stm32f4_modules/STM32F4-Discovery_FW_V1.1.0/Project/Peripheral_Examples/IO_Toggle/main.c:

/**
  ******************************************************************************
  * @file    IO_Toggle/main.c 
  * @author  MCD Application Team
  * @version V1.0.0
  * @date    19-September-2011
  * @brief   Main program body
  ******************************************************************************
  * @attention
  *
  * THE PRESENT FIRMWARE WHICH IS FOR GUIDANCE ONLY AIMS AT PROVIDING CUSTOMERS
  * WITH CODING INFORMATION REGARDING THEIR PRODUCTS IN ORDER FOR THEM TO SAVE
  * TIME. AS A RESULT, STMICROELECTRONICS SHALL NOT BE HELD LIABLE FOR ANY
  * DIRECT, INDIRECT OR CONSEQUENTIAL DAMAGES WITH RESPECT TO ANY CLAIMS ARISING
  * FROM THE CONTENT OF SUCH FIRMWARE AND/OR THE USE MADE BY CUSTOMERS OF THE
  * CODING INFORMATION CONTAINED HEREIN IN CONNECTION WITH THEIR PRODUCTS.
  *
  * <h2><center>&copy; COPYRIGHT 2011 STMicroelectronics</center></h2>
  ******************************************************************************  
  */ 

/* Includes ------------------------------------------------------------------*/
#include "stm32f4_discovery.h"
#include "stm32f4xx_gpio.h"
#include "stm32f4xx_rcc.h"
#include "stm32f4xx.h"

/** @addtogroup STM32F4_Discovery_Peripheral_Examples
  * @{
  */

/** @addtogroup IO_Toggle
  * @{
  */ 

/* Private typedef -----------------------------------------------------------*/
GPIO_InitTypeDef  GPIO_InitStructure;

/* Private define ------------------------------------------------------------*/
/* Private macro -------------------------------------------------------------*/
/* Private variables ---------------------------------------------------------*/
/* Private function prototypes -----------------------------------------------*/
void Delay(__IO uint32_t nCount);
/* Private functions ---------------------------------------------------------*/

/**
  * @brief  Main program
  * @param  None
  * @retval None
  */
int main(void)
{
  /*!< At this stage the microcontroller clock setting is already configured, 
       this is done through SystemInit() function which is called from startup
       file (startup_stm32f4xx.s) before to branch to application main.
       To reconfigure the default setting of SystemInit() function, refer to
        system_stm32f4xx.c file
     */

  /* GPIOD Periph clock enable */
  RCC_AHB1PeriphClockCmd(RCC_AHB1Periph_GPIOD, ENABLE);

  /* Configure PD12, PD13, PD14 and PD15 in output pushpull mode */
  GPIO_InitStructure.GPIO_Pin = GPIO_Pin_12 | GPIO_Pin_13| GPIO_Pin_14| GPIO_Pin_15;
  GPIO_InitStructure.GPIO_Mode = GPIO_Mode_OUT;
  GPIO_InitStructure.GPIO_OType = GPIO_OType_PP;
  GPIO_InitStructure.GPIO_Speed = GPIO_Speed_100MHz;
  GPIO_InitStructure.GPIO_PuPd = GPIO_PuPd_NOPULL;
  GPIO_Init(GPIOD, &GPIO_InitStructure);

  // Enable clock for GPIOA
    RCC_AHB1PeriphClockCmd(RCC_AHB1Periph_GPIOA, ENABLE);
  // Configure PA0 as push-pull output
    GPIO_InitStructure.GPIO_Pin = GPIO_Pin_0 | GPIO_Pin_1;
    GPIO_InitStructure.GPIO_Speed = GPIO_Speed_100MHz;
    GPIO_InitStructure.GPIO_Mode = GPIO_Mode_OUT;
    GPIO_InitStructure.GPIO_OType = GPIO_OType_PP;
    GPIO_Init(GPIOA, &GPIO_InitStructure);

  while (1)
  {

        /* Toggle LED on PA0 */
        // Reset bit will turn on LED (because the logic is interved)
        GPIO_ResetBits(GPIOA, GPIO_Pin_0);
        Delay(0x2FFFFF);
        GPIO_ResetBits(GPIOA, GPIO_Pin_1);
        Delay(0x2FFFFF);
        // Set bit will turn off LED (because the logic is interved)
        GPIO_SetBits(GPIOA, GPIO_Pin_0);
        Delay(0x2FFFFF);
        GPIO_SetBits(GPIOA, GPIO_Pin_1);
        Delay(0x2FFFFF);



    /* PD12 to be toggled */
//    GPIO_SetBits(GPIOD, GPIO_Pin_12);
    
    /* Insert delay */
//    Delay(0x3FFFFF);
    
    /* PD13 to be toggled */
//    GPIO_SetBits(GPIOD, GPIO_Pin_13);
    
    /* Insert delay */
//    Delay(0x3FFFFF);
  
    /* PD14 to be toggled */
//    GPIO_SetBits(GPIOD, GPIO_Pin_14);
    
    /* Insert delay */
//    Delay(0x3FFFFF);
    
    /* PD15 to be toggled */
//    GPIO_SetBits(GPIOD, GPIO_Pin_15);
    
    /* Insert delay */
//    Delay(0x7FFFFF);
    
//    GPIO_ResetBits(GPIOD, GPIO_Pin_12|GPIO_Pin_13|GPIO_Pin_14|GPIO_Pin_15);
    
    /* Insert delay */
//    Delay(0xFFFFFF);
  }
}

/**
  * @brief  Delay Function.
  * @param  nCount:specifies the Delay time length.
  * @retval None
  */
void Delay(__IO uint32_t nCount)
{
  while(nCount--)
  {
  }
}

#ifdef  USE_FULL_ASSERT

/**
  * @brief  Reports the name of the source file and the source line number
  *         where the assert_param error has occurred.
  * @param  file: pointer to the source file name
  * @param  line: assert_param error line source number
  * @retval None
  */
void assert_failed(uint8_t* file, uint32_t line)
{ 
  /* User can add his own implementation to report the file name and line number,
     ex: printf("Wrong parameters value: file %s on line %d\r\n", file, line) */

  /* Infinite loop */
  while (1)
  {
  }
}
#endif

/**
  * @}
  */ 

/**
  * @}
  */ 

/******************* (C) COPYRIGHT 2011 STMicroelectronics *****END OF FILE****/

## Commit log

2020-04-08 solid state relays
2020-04-08 Pi mh
2020-04-08 cap flipped
2020-04-08 Pi3 added
2020-04-08 supply schema
2020-04-09 added barrel_connector and 3v3 reg libraries, added connections on supply sheet
2020-04-09 added power connections and a led
2020-04-09 clean up
2020-04-09 rtc added
2020-04-09 RTC to PCB
2020-04-09 AQH3213AX added
2020-04-10 added miscellaneous to electro valves sheet
2020-04-10 .bck files purged
2020-04-10 AQH3213AX footprint fixed
2020-04-10 3d model for phototriac
2020-04-10 I/O EXPANDER added
2020-04-10 Made symbol paths relative to project's root
2020-04-10 connecting relays to the i2c-gpios
2020-04-10 3D model for motor driver
2020-04-12 replacememnt
2020-04-12 connecting esp32 signals
2020-04-12 added connections to ElectroValves sheet
2020-04-12 added SOT-223 3d shape
2020-04-12 pcb/keep_breathing_ctrl.kicad_pcb-bak removed
2020-04-12 led drive transistors
2020-04-13 Barrel jack 3d shape
2020-04-13 added footprints in supply sheet
2020-04-13 Connections in the schema were modified and components some components from supply and electrovalves were positioned on the PCB
2020-04-13 GND isolated for motor driver
2020-04-13 ISO7762 added
2020-04-13 UCC12040 added
2020-04-14 footprints for isolation
2020-04-14 powerstepper placement
2020-04-14 updating cooper pour
2020-04-15 *.kicad_pcb were modified, a sheet was created for rapsberry connector
2020-04-16 STM32 added
2020-04-16 Adición del STM32
2020-04-16 Adición del STM32F4
2020-04-16 STM32F4 fix
2020-04-16 replacement
2020-04-16 connecting STM32
2020-04-16 environmental sensors
2020-04-16 footprints
2020-04-17 getting roo for sensors
2020-04-18 sensor array started
2020-04-18 array sensor improved
2020-04-19 shield connector fixed:
2020-04-19 all i2c from shields to FPGA
2020-04-19 array of connectors replacment
2020-04-19 schematic simplified
2020-04-20 stepper planes
2020-04-20 added ice40 regulators
2020-04-20 SPI connections between FPGA, PI and FLASH
2020-04-20 Added 3V3_STM in STM32F4 and supply sheets
2020-04-21 stm32 jtag connected
2020-04-21 GND for motor driver
2020-04-21 rtc placement
2020-04-21 support connectors
2020-04-22 spi flash placement
2020-04-22 FPGA rotation
2020-04-22 routing i2c signals
2020-04-22 SS_SPI_CLK shortcut fixed
2020-04-23 improving shield stability
2020-04-23 2.5V diode placement
2020-04-23 3v3_ice removed
2020-04-23 fixing i2c sensors
2020-04-23 small 1.2V reg
2020-04-23 footprint fix
2020-04-23 SPI for sensor shield array
2020-04-23 routing analog signals
2020-04-23 analog signals routed
2020-04-24 routing...
2020-04-24 rotate
2020-04-24 fixing RPi mounting holes
2020-04-24 1.2v ldo changed
2020-04-25 routing....
2020-04-25 solid state stm32's signals connected
2020-04-25 connecting SPI signals from STM32
2020-04-25 routing spi from stepper driver
2020-04-26 unconnected PSU
2020-04-26 TCR8BM12 lib added
2020-04-26 protection circuit added
2020-04-27 mounting holes
2020-04-28 adding mounting holes
2020-04-28 new 1.2V DC-DC
2020-04-28 3v3 torex reg
2020-04-28 torex dc-dc module
2020-04-28 ferrite bead added
2020-04-28 XCL214 placement
2020-04-28 power connector
2020-04-29 placement
2020-05-02 relayout
2020-05-02 stepper motor connector changed
2020-05-02 relays placement
2020-05-04 routing isolators
2020-05-04 updating planes
2020-05-04 UCC12040 fixed
2020-05-05 fixing missed footprints
2020-05-05 decoupling caps for stm32
2020-05-05 i2c stuff
2020-05-05 nss connected
2020-05-05 CERN Open Hardware Licence Version 2 - Permissive
2020-05-06 stm32 boot modes connected to the Pi
2020-05-06 adding external spi
2020-05-06 relay VCC fixed
2020-05-07 recomendations from Carlos Camargo applied
2020-05-07 2 CS for FPGA
2020-05-07 top view
2020-05-07 bottom view
2020-05-11 jumper for reley voltage selector
2020-05-11 relay power from main conector
2020-05-11 improving cooper pours
2020-05-11 buzzer added to libs
2020-05-12 improving ground separation
2020-05-22 Solved connections showed wrong by ERC
2020-05-23 Buzzer circuit on schema
2020-05-23 Buzzer circuit on PCB
2020-05-24 Solved problems with POWERSTEP01 footprint
2020-05-24 Solved connection problem with XCL214B333DR and it was added 3 leds to the board
2020-05-25 Changed 5V_r 12V 24V and 48V to thermal reliefs
2020-05-25 Solved all troubles with Torex footprints and copper zones
2020-05-25 new fixed modules for TOREX_XCL2144B123DR and powerSTEP01
2020-05-25 Changed 3V3 and GND connections on STM32 and TOREX
2020-05-25 changed position for capacitors on STM32
2020-05-26 Changes on STM and ICE paths
2020-06-03 Added two SSR AQH3223AX on schema
2020-06-04 Added two SSR on PCB
2020-06-05 Added all connections between STM and AQH3223. added pin header with GPIO from STM
2020-06-07 Added 3d shape for connector clik-mate Added connection between STM and connector clik-mate on schema and PCB P3 is a connector that allows put a panic button for do a reset in the IC powerstep01
2020-06-09 Chaged P3 to SW1 and a new circuit to emergency reset on IC powerstep01 Added 3d shape for 2 contancs molex clik-mate connector
2020-06-25 Added the subproject pressure sensor module
2020-06-25 - Added Sensor_pressure library - Added 3d shape for MPX5100 sensor - MPX5100 footprint created - Connections on SEEschema for presure_sensor_module - Connections on PCBnew for pressure_sensor_module
2020-06-25 - Added footprint MPX100 vertical - Modified pinHeader footprints to SMD
2020-06-25 - Modified pin 1 to square in MPX5100 footprint - added another 3d shape for MPX 5100GP
2020-07-02 added an LM358 to improve possible problems with impedance between the sensor and the STM
2020-07-02 Added readme.txt in pressure_sensor_module
2020-07-05 Only a plot for gerber files
2020-07-09 Added footprint for ABPDJJ001PDSA3 sensor Created daugther PCB for ABPDJJ001PDSA3 sensor in EESchema and PCBnew
2020-07-10 Added daugther board for ABPDANT060MGAA5 sensor on EESchema and PCBnew Added ABPDANT060MGAA5 library and footprint
2020-07-10 Added board for ABPDANT015PGAA5 sensor added ABPDANT015PGAA5 lib
2020-07-10 Added DigiKey part number to J2 connector WM17456-ND
2020-07-10 Added DigiKey part number
2020-07-10 Added capacitors DigiKey part number
2020-07-10 Added DigiKey parts number
2020-07-11 Added components dikey part numbers in modified sheets
2020-07-11 Added basic shape 3d for ABPDJJ001PDSA3 sensor
2020-07-11 Added digiKey part number for some components
2020-07-11 Added BOM for PCB ABPDANT015PGAA5 sensor
2020-08-04 Added all references on silkscreen added BOM for sensor modules
2020-08-05 Added kicad design with 4 pressure sensors for daugthers PCB Added DigiKey number for power connector
2020-08-05 new gerber files
2020-08-05 Added mouse bites for pressure sensors PCB
2020-08-05 created new gerber files
2020-09-16 Added blink example for ice40 FPGA Added icespiprog.c source file for config ice40 FPGA
2020-09-16 README.MD added
2020-09-16 momdified readme.md
2020-11-23 Added some examples to programming the processor
2020-12-04 Added and example to read all Analog signals in S0 to S8 connectors
2020-12-04 Deleted all .o files
2021-01-10 Added blinky and Uart example with Zephyr RTOS
2021-09-16 Nueva version para ventilador electroneumatico
2021-09-30 driver for motor eliminated
2021-11-05 Position for J2 U1 and U2 modified
2021-11-05 Modified J2 position
2021-11-05 J2 connector modified
2022-02-02 Modified sensor modules and created module for 403-SFM3020 sensor
2022-05-26 PCB for oxygen sensor
2022-05-27 Gerber files created
2023-04-05 BOM updated and 3D shape for bornier added
2023-04-05 FreeCAD file deleted
